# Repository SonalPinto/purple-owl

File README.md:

# Purple Owl

The Purple Owl is a uniform row staggered 60% keyboard designed around ortholinear 1u keycaps and hotswap sockets.

## News
- The prototype appeared on KBD.news! [Link](https://kbd.news/Purple-Owl-1581.html)
- 🎉 PurpleOwl wins 2nd place 🥈 in the [XIAO Mechanical Keyboard Contest](https://www.seeedstudio.com/seeed-fusion-diy-xiao-mechanical-keyboard-contest.html) 🎉

## Layout
The Purple Owl was inspired off the works of Ziptyze with their Zlant (4x12) and ZlantXL (5x12). It is almost like a staggered 5-row Preonic but with more columns a narrow bottom row to offer the visual aesthetic of four dominant rows like a Plank. Each row has a 0.25u stagger unlike a traditional row-stagger. There are 14 columns to accommodate the outer symbols (`-=[]\`). The right shift can be traded in for an arrow cluster. The ctrl, shift and other mods are designed to be under the thumbs with a symmetric bottom row that has a 2u surrounded by two 1u on each side. The board runs on [KMK](http://kmkfw.io/), so the keys can be freely mapped.

Link to the base layout at [Keyboard Layout Editor](http://www.keyboard-layout-editor.com/#/gists/7c51d0df5eb78da5dd614ee6019f13bc). KLE Raw is also available [here](purple-owl-kle.txt)

## Electronics
Instead of a traditional diode matrix, the Purple Owl implements a **scan chain** to poll the state of its switches using only 3 logic pins. This opens the door to support a wide variety of off-the-shelf microcontrollers including the Pro Micro layout variants popular in the mechanical keyboard community. KMK supports a scan chain scanner by default. So, any CircuitPython compatible board with the pinouts shown below should snap into Purple Owl. There is a solder jumper to select between two popular layouts - the Pro Micro variant and the Seeed XIAO variant. The Purple Owl design needs two power pins (3V3 and GND) and three logic pins (CLK, DATA, LATCH).

> While, I currently have a bunch of RP2040 boards in various layouts, I eventually might test out KMK BLE wireless with some CircuitPython compatible nrf52840 board like the nice!nano, [Seeed nrf52840](https://www.seeedstudio.com/Seeed-XIAO-BLE-Sense-nRF52840-p-5253.html) or Adafruit QTPy Bluefruit (doesn't exist yet?). Anything with a JST connector for the battery.

## Seeed XIAO Mechanical Keyboard Contest
I came across an article for this [contest](https://www.seeedstudio.com/seeed-fusion-diy-xiao-mechanical-keyboard-contest.html) on [KBD.news](https://kbd.news/). The Purple Owl was designed to be powered by a [Seeed XIAO RP2040](https://www.seeedstudio.com/XIAO-RP2040-v1-0-p-5026.html) (or any CircuitPython compatible Seeed XIAO for that matter) and will be my entry in the contest! Seeed is sponsoring two fully [assembled PCBs](https://www.seeedstudio.com/pcb-assembly.html) - and that is an opportunity I simply couldn't pass on.

The tiny size of the Seeed XIAO RP2040 will be perfect to highlight the GPIO-efficient scan-chain design. Aside from the 61 switches, the Seeed XIAO RP2040 will drive 16 underglow LEDs which will look stunning in a laser cut case.

## Gallery

## PCB

### Externals
- Acheron MX footprints ([link](https://github.com/AcheronProject/acheron_MXH.pretty.git)) for Kailh hotswap sockets.
- Geometric animals art for the silkscreen ([link](https://www.etsy.com/listing/873524342/geometric-animals-bundle-svg-linear]))
- JLCPCB Tools for Kicad ([link](https://github.com/Bouni/kicad-jlcpcb-tools)) to generate the gerbers and assembly files for JLCPCB.

### Prototype v0.1
To get a feel for the layout I prototyped a board that runs off a RP2040 microcontroller, the Waveshare RP2040 Zero. When I started the prototype, I intended for the the final Purple Owl PCB to have all electronics integrated on the board, including the RP2040. The prototype PCB is simply a diode matrix of hotswap sockets and diodes hooked up to the Zero. No LEDs or anything fancy yet.

I referred to the "recommended minimums" on [Acheron Setup](http://acheronproject.com/acheron_setup/acheron_setup/) for board rules which are more constrained for some fields that the default JLCPCB setup. Laying out the switches is a cakewalk once you set the grid to 19.05mm (1u or 0.75in). For the stagger, set the grid to 4.7625mm (0.25u or 19.05/4mm). The controller is tilted by 26' which is along the ~~z~~slant of the columns.

I checked for clearance pretty early on as soon as I had the swtiches and controller laid out to make sure the slightly tilted controller and USB cable seemed ok on the right side. I printed half(~ish) the layout flipped on paper to scale.

For assembly, I wanted to trial JLCPCB's assembly service - especially for hotswap sockets. While, I could simply solder the sockets myself, I was curious about JLCPCB's work. And, if it did work, then building the proper Purple Owl would be fairly turnkey.

The footprint for the JLCPCB [part](https://jlcpcb.com/partdetail/Kailh-CPG151101S11/C2803348) for the Kailh hotswap socket is centered around the socket itself. But, the switch footprint on the PCB is centered around the stem hole. So, I wrote a [small python snippet](pcb/tools/fix_pos.py) to fix the socket position and rotation in the POS assembly file. Below, you can see how it looks before (right) and after (left) the fix on the JLCPCB assembly preview.

The cost for the PCB fabrication and assembly came up to $85 for 5 boards assembled. The 305 hotswap sockets (61 per board) going at 78 cents a piece for a total of about $24. In hindsight, I should have just assembled 2 boards considering this was a prototype, but my excitement got the better of me.

> Firmware Note: The Zero supports CircuitPython and thus, KMK. So, not much work to be done aside from the KMK config for the matrix. I'd need to add CircuitPython support for the RP2040 layout integrated on the proper Purple Owl (if I went that route), but that seems easy looking at [how it was ported](https://sourcegraph.com/github.com/adafruit/circuitpython/-/tree/ports/raspberrypi/boards/waveshare_rp2040_zero) for the Zero.

### Revelation: The Scan Chain

A while back, I had considered shift registers for scanning the switch matrix in passing when I had read this [Hackaday article](https://hackaday.com/2018/09/30/whats-the-cheapest-way-to-scan-lots-of-buttons/). Along the lines of using 2 shift registers for an 8x8 matrix - one serial-to-parallel to drive the columns and a parallel-to-serial to poll the rows. While this would use only two 8-bit shift registers, I'd still need diodes per switch for NKRO. However, I'd need no more than 5-6 pins to interface with the switch matrix over the two shift registers. At first glance, the approach didn't really seem any better than using a traditional diode matrix and routing the columns and rows to the IOs of the microcontroller (especially since I was considering integrating the RP2040 on the board).

Then, I stumbled upon an article for the [Hello World Smart Keyboard](https://kbd.news/Hello-Word-Smart-Keyboard-1569.html) project when Dovenyi posted their [#89 issue of the KBD News Digest](https://www.reddit.com/r/MechanicalKeyboards/comments/wdgbuy/keyboard_builders_digest_issue_89/) on r/mk. It was a curiously interesting design with 74HC165 shift registers polling _all_ switches latched in parallel along a 1xN matrix. Surely, this would need a lot of shift registers (one IC per 8 keys) and pull up resistors per switch. So, in terms of parts, the design used relatively more parts (and proper active components). Nonetheless, the most attractive part of the design was that it needed merely 3 pins to interface with the matrix.

While I was running a embarrassingly one-sided rubber ducking session with Dovenyi on that reddit thread, I realized something. Using fewer fins suddenly opens up a design where I can attach off-the-shelf (OTS) microcontroller boards right in between the switches (alongside the hotswap sockets) - underneath the switches and not on the side. Because, I'd only need to solder enough headers for functional and mechanical purpose. I could use something tiny like a [Adafruit QTPy RP2040](https://www.adafruit.com/product/4900) or [Pimoroni Tiny RP2040](https://shop.pimoroni.com/products/tiny-2040?variant=39560012234835) and merely use just one side of the pins between the sockets, and some on the other side for mechanical stability.

These uC (microcontroller) boards are typically 700mil wide with their columns of pins 600mil apart. They don't fit around hotswap sockets if you are using all the pins. It does work for soldered switch footprints like in the case of ErgoDash or ErgoTravel, but not for hotswap sockets because of the wider footprint. Hence, in the prototype I had the uC on the side. Secondly, the uC boards that have enough pins for a diode matrix are typically longer than 1U and won't fit across the rows of a row-staggered layout (while they do work for ortho or column staggered layouts). Now, these problems are washed out when you realize that you don't need to drill and solder headers for _all_ the pins. Just enough to get the job done. And, you don't really need to use a small board like the QTPy. Even a KB2040 would work - since you don't have to drill holes across the rows to access all the pins.

I had almost gone down the path of designing an integrated RP2040 board. Researched a bunch of popular designs and minimal RP2040 circuits, and printed all their schematics. I had even picked out the parts on LCSC and had calculated the trace widths and separation required for the differential pair routing for the USB Full Speed mode (90ohm Z_diff). Because I didn't think there was a _good_ design I where I could have the uC board underneath and not on the side...

And now, there was a way.

> Firmware Note: Looks like KMK has a scanner for shift registers ([see](https://github.com/KMKfw/kmk_firmware/blob/master/kmk/scanners/keypad.py)) that wraps CircuitPython's `keypad.ShiftRegisterKeys()`. Great!

### Production v1.0
The design uses 8 74HC165 (TSSOP-16 package) to form the scan chain. 7 of these poll the top 4 rows across 14 columns and the last one polls the bottom row. I've also added 16 underglow LEDs (WS2812B-V5). The scan chain for the first 6 columns is shown below.

Compared to the prototype, the design now has a clean board edge tightly fitting the switches, since the uC now goes underneath. The uC is socketed to the board with through-hole headers. Out of the 14 pins of the Seeed XIAO RP2040, 11 are connected.

There are jumpers to select the 3V3 source depending on the attached uC. And jumpers to select the power source (3.3V or 5V) for the LEDs. Though off-spec, The LEDs work fine on 3.3V, albeit slightly less bright than if powered by 5V. There wasn't enough space (while staying close to the board edge) to allow a through hole header for the 5V, so the design offers a jumper/through-hole that needs to be wired between the board and the jumper site if 5V is desired.

- JP1: Join `1-2` or `2-3` depending on where the 3V3 pin on the uC is. For the Seeed XIAO RP2040 variants short the `1-2`. And, for Pro Micro variants, short `2-3`.
- JP2: Join `1-2` to select the 3.3V source selected by JP1, or connect the 5V to `3` from the uC over a wire and join `2-3`.

For assembly, Seeed is sponsoring two fully assembled boards 🎉

## Firmware

This project was my first experience with CircuitPython, let alone KMK. I am stunned how wasy it was to work with. Never did I think it would take just few lines of python to establish a fully functional keyboard with layers and underglow LEDs.

There are bringup scripts for the both PCB variants which test the PCB and demonstrate interfacing with the keyboard switches using native CircuitPython.
- [v0.1 bringup](firmware/v0.1/bringup.py) - diode matrix.
- [v1.0 bringup](firmware/v1.0/bringup.py) - scan chain. Using digitalio, it took about 1ms to scan 61 switches. 

The [setup](firmware/v0.1/main.py) for the prototype v0.1 diode matrix was fairly straightforward with KMK. I included three basic layers to start with (I really need the tilde/grave in my line of work). The physical layout of the switches were mapped to the layout with the `coord_mapping` setup.

The [build](firmware/v1.0/main.py) for the v1.0 PCB inherited the same layers. The firmware switched the `scanner` to the `ShiftRegisterKeys()` and updated the `coord_mapping` to the physical layout of the scan chain. KMK offeres a neat `RGB` extension to support the underglow LEDs. The underglow RGB controls are added on a layer. Looking at the sheer simplicity of the [RGB extension](https://github.com/KMKfw/kmk_firmware/blob/master/kmk/extensions/rgb.py) I might consider writing a fancy underglow mode or two. Since, this was a *proper* build, the [`boot.py`](firmware/v1.0/boot.py) was updated with a "dev mode" which hides CircuitPython enumerations (serial, midi and storage) except for the USB HID keyboard.

## Laser cut case

For the case, I had envisioned a laser cut case with 1/8" acrylic layers. With the top layers as dark and the bottom layer as translucent to diffuse the underglow. This was the first time I used Fusion360 as well. Lots of firsts for me in this project. Thankfully, there are a ton of YouTube videos to learn from, and I only need the basics of sketching in 2D to set up the layers for the laser cut case.

Using [plate.keeb.io](https://plate.keeb.io/) I obtained the cut outs for the switches and stabilizer to form the top switch plate. Then, I designed the middle layers to be spaced around the PCB by importing the PCB edge-cuts layer into the design and offset it. All the layers except for the top switch plate have cut outs for the Seeed XIAO RP2040 that is on the underside of the PCB. All the holes are cut out for M2 hardware. I also added holes for some feet that I found on [FlashQuark](https://flashquark.com/product/aluminum-keyboard-feet-set-of-2/). The links to the files for the laser cut case are below.

- [top](case/top.dxf)
- [middle](case/middle.dxf)
- [bottom](case/bottom.dxf)

I used p95 matte black acrylic sourced from a local [TAP plastics](https://www.tapplastics.com/plastics/custom-cut-to-size-plastic-sheets/acrylic-plexiglass-sheets) for the top three layers (1xtop, 2xmiddle), and a satinice acrylic for the bottom layer.

## Credits
- Layout inspired by Ziptyze's [Zlant](https://1upkeyboards.com/shop/keyboard-kits/diy-40-kits/zlant-40-acrylic-keyboard-kit/) and [ZlantXL](https://1upkeyboards.com/shop/keyboard-kits/diy-40-kits/zlantxl-50-mechanical-keyboard-kit/).
- Electronics inspired by Zhihui's [HanWen](https://github.com/peng-zhihui/HelloWord-Keyboard) and Tzarc's [Ghoul](https://github.com/tzarc/ghoul) which use shift registers to scan the matrix.
- Dovenyi and [Keyboard Builder's Digest](https://kbd.news/).
- Seeed DIY XIAO Mechanical Keyboard Contest, [Link](https://www.seeedstudio.com/seeed-fusion-diy-xiao-mechanical-keyboard-contest.html).
- Photography by Wife 😘.

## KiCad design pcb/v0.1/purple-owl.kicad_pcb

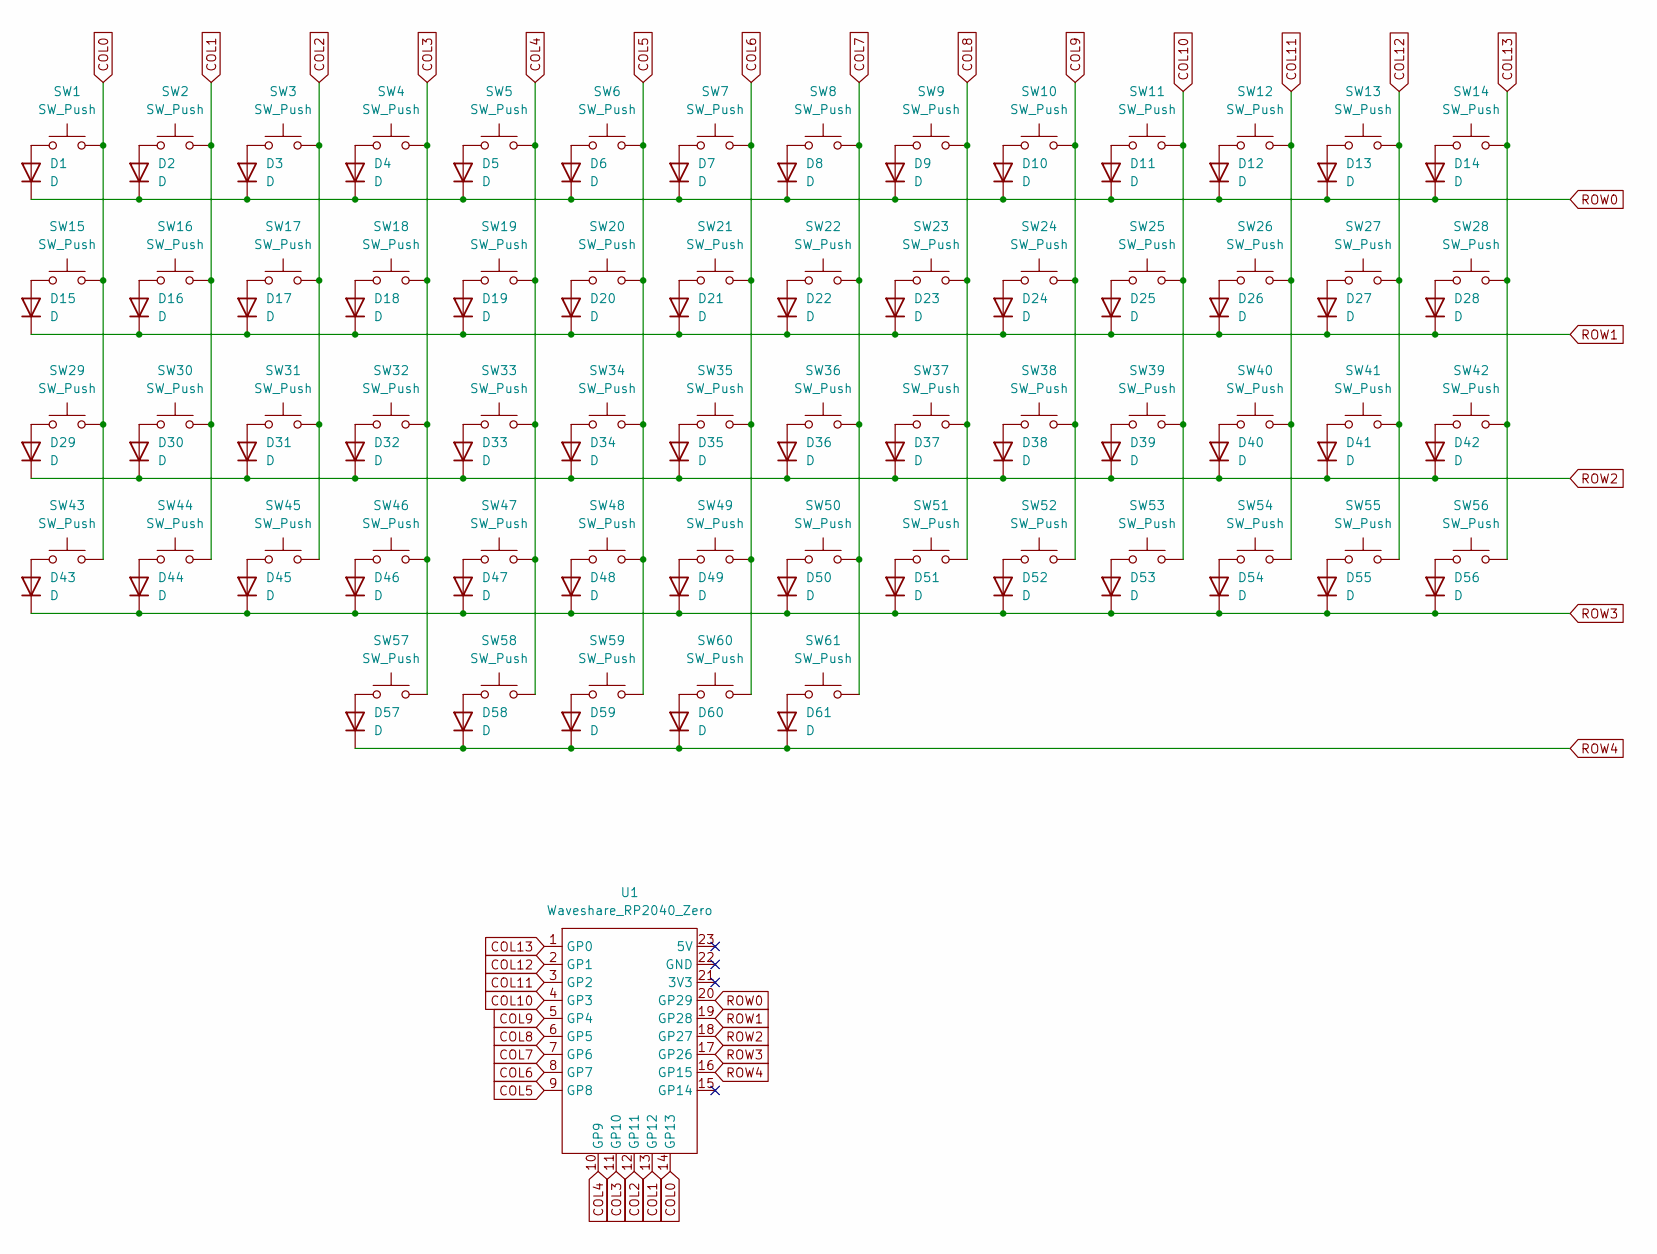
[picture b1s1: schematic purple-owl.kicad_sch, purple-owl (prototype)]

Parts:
D1, D2, D3, D4, D5, D6, D7, D8, D9, D10, D11, D12, D13, D14, D15, D16, D17, D18, D19, D20, D21, D22, D23, D24, D25, D26, D27, D28, D29, D30, D31, D32, D33, D34, D35, D36, D37, D38, D39, D40, D41, D42, D43, D44, D45, D46, D47, D48, D49, D50, D51, D52, D53, D54, D55, D56, D57, D58, D59, D60, D61: D; D_SOD-123
SW1, SW2, SW3, SW4, SW5, SW6, SW7, SW8, SW9, SW10, SW11, SW12, SW13, SW14, SW15, SW16, SW17, SW18, SW19, SW20, SW21, SW22, SW23, SW24, SW25, SW26, SW27, SW28, SW29, SW30, SW31, SW32, SW33, SW34, SW35, SW36, SW37, SW38, SW39, SW40, SW41, SW42, SW43, SW44, SW45, SW46, SW47, SW48, SW49, SW50, SW51, SW52, SW53, SW54, SW55, SW56, SW57, SW58, SW60, SW61: SW_Push; MX100H
SW59: SW_Push; MX200HR
U1: Waveshare_RP2040_Zero

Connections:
COL0: SW1.2, SW15.2, SW29.2, SW43.2, U1.14 (GP13)
COL1: SW2.2, SW16.2, SW30.2, SW44.2, U1.13 (GP12)
COL2: SW3.2, SW17.2, SW31.2, SW45.2, U1.12 (GP11)
COL3: SW4.2, SW18.2, SW32.2, SW46.2, SW57.2, U1.11 (GP10)
COL4: SW5.2, SW19.2, SW33.2, SW47.2, SW58.2, U1.10 (GP9)
COL5: SW6.2, SW20.2, SW34.2, SW48.2, SW59.2, U1.9 (GP8)
COL6: SW7.2, SW21.2, SW35.2, SW49.2, SW60.2, U1.8 (GP7)
COL7: SW8.2, SW22.2, SW36.2, SW50.2, SW61.2, U1.7 (GP6)
COL8: SW9.2, SW23.2, SW37.2, SW51.2, U1.6 (GP5)
COL9: SW10.2, SW24.2, SW38.2, SW52.2, U1.5 (GP4)
COL10: SW11.2, SW25.2, SW39.2, SW53.2, U1.4 (GP3)
COL11: SW12.2, SW26.2, SW40.2, SW54.2, U1.3 (GP2)
COL12: SW13.2, SW27.2, SW41.2, SW55.2, U1.2 (GP1)
COL13: SW14.2, SW28.2, SW42.2, SW56.2, U1.1 (GP0)
unnamed: D1.2 (A), SW1.1
unnamed: D2.2 (A), SW2.1
unnamed: D3.2 (A), SW3.1
unnamed: D4.2 (A), SW4.1
unnamed: D5.2 (A), SW5.1
unnamed: D6.2 (A), SW6.1
unnamed: D7.2 (A), SW7.1
unnamed: D8.2 (A), SW8.1
unnamed: D9.2 (A), SW9.1
unnamed: D10.2 (A), SW10.1
unnamed: D11.2 (A), SW11.1
unnamed: D12.2 (A), SW12.1
unnamed: D13.2 (A), SW13.1
unnamed: D14.2 (A), SW14.1
unnamed: D15.2 (A), SW15.1
unnamed: D16.2 (A), SW16.1
unnamed: D17.2 (A), SW17.1
unnamed: D18.2 (A), SW18.1
unnamed: D19.2 (A), SW19.1
unnamed: D20.2 (A), SW20.1
unnamed: D21.2 (A), SW21.1
unnamed: D22.2 (A), SW22.1
unnamed: D23.2 (A), SW23.1
unnamed: D24.2 (A), SW24.1
unnamed: D25.2 (A), SW25.1
unnamed: D26.2 (A), SW26.1
unnamed: D27.2 (A), SW27.1
unnamed: D28.2 (A), SW28.1
unnamed: D29.2 (A), SW29.1
unnamed: D30.2 (A), SW30.1
unnamed: D31.2 (A), SW31.1
unnamed: D32.2 (A), SW32.1
unnamed: D33.2 (A), SW33.1
unnamed: D34.2 (A), SW34.1
unnamed: D35.2 (A), SW35.1
unnamed: D36.2 (A), SW36.1
unnamed: D37.2 (A), SW37.1
unnamed: D38.2 (A), SW38.1
unnamed: D39.2 (A), SW39.1
unnamed: D40.2 (A), SW40.1
unnamed: D41.2 (A), SW41.1
unnamed: D42.2 (A), SW42.1
unnamed: D43.2 (A), SW43.1
unnamed: D44.2 (A), SW44.1
unnamed: D45.2 (A), SW45.1
unnamed: D46.2 (A), SW46.1
unnamed: D47.2 (A), SW47.1
unnamed: D48.2 (A), SW48.1
unnamed: D49.2 (A), SW49.1
unnamed: D50.2 (A), SW50.1
unnamed: D51.2 (A), SW51.1
unnamed: D52.2 (A), SW52.1
unnamed: D53.2 (A), SW53.1
unnamed: D54.2 (A), SW54.1
unnamed: D55.2 (A), SW55.1
unnamed: D56.2 (A), SW56.1
unnamed: D57.2 (A), SW57.1
unnamed: D58.2 (A), SW58.1
unnamed: D59.2 (A), SW59.1
unnamed: D60.2 (A), SW60.1
unnamed: D61.2 (A), SW61.1
ROW0: D1.1 (K), D2.1 (K), D3.1 (K), D4.1 (K), D5.1 (K), D6.1 (K), D7.1 (K), D8.1 (K), D9.1 (K), D10.1 (K), D11.1 (K), D12.1 (K), D13.1 (K), D14.1 (K), U1.20 (GP29)
ROW1: D15.1 (K), D16.1 (K), D17.1 (K), D18.1 (K), D19.1 (K), D20.1 (K), D21.1 (K), D22.1 (K), D23.1 (K), D24.1 (K), D25.1 (K), D26.1 (K), D27.1 (K), D28.1 (K), U1.19 (GP28)
ROW2: D29.1 (K), D30.1 (K), D31.1 (K), D32.1 (K), D33.1 (K), D34.1 (K), D35.1 (K), D36.1 (K), D37.1 (K), D38.1 (K), D39.1 (K), D40.1 (K), D41.1 (K), D42.1 (K), U1.18 (GP27)
ROW3: D43.1 (K), D44.1 (K), D45.1 (K), D46.1 (K), D47.1 (K), D48.1 (K), D49.1 (K), D50.1 (K), D51.1 (K), D52.1 (K), D53.1 (K), D54.1 (K), D55.1 (K), D56.1 (K), U1.17 (GP26)
ROW4: D57.1 (K), D58.1 (K), D59.1 (K), D60.1 (K), D61.1 (K), U1.16 (GP15)

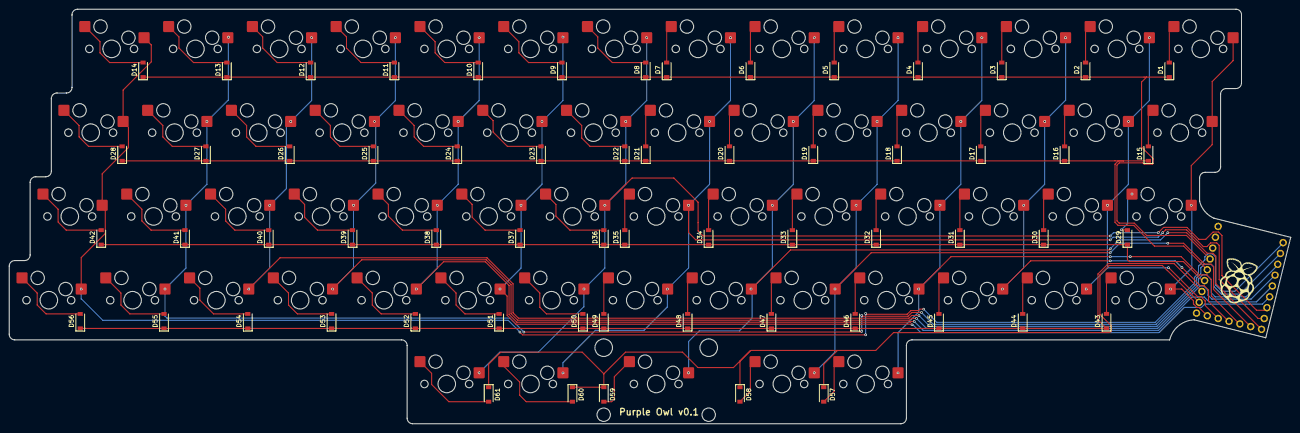
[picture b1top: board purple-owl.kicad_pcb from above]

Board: 2 copper layers, 291.4 x 94.3 mm, 123 parts (1 on the bottom side), 80 nets.

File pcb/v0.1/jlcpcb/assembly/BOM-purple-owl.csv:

Comment,Designator,Footprint,LCSC
SW_Push,"SW1,SW10,SW11,SW12,SW13,SW14,SW15,SW16,SW17,SW18,SW19,SW2,SW20,SW21,SW22,SW23,SW24,SW25,SW26,SW27,SW28,SW29,SW3,SW30,SW31,SW32,SW33,SW34,SW35,SW36,SW37,SW38,SW39,SW4,SW40,SW41,SW42,SW43,SW44,SW45,SW46,SW47,SW48,SW49,SW5,SW50,SW51,SW52,SW53,SW54,SW55,SW56,SW57,SW58,SW59,SW6,SW60,SW61,SW7,SW8,SW9",MX100H,C2803348
D,"D1,D10,D11,D12,D13,D14,D15,D16,D17,D18,D19,D2,D20,D21,D22,D23,D24,D25,D26,D27,D28,D29,D3,D30,D31,D32,D33,D34,D35,D36,D37,D38,D39,D4,D40,D41,D42,D43,D44,D45,D46,D47,D48,D49,D5,D50,D51,D52,D53,D54,D55,D56,D57,D58,D59,D6,D60,D61,D7,D8,D9",D_SOD-123,C81598

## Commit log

2022-07-31 First Commit
    - Add Purple Owl prototype PCB
    - Purple Owl kicad symbols and footprints
    - README
2022-08-02 Add QTPy RP2040 symbol and footprint
    - Add Adafruit QTPy RP2040 symbol and footprint
    - Update story on README
2022-08-03 Update README with WIP badge
2022-08-04 Open pcb design for v1.0
    - Schematic for v1.0 with 74HC165 shift registers for the 61 keys
    - Matrix is polled using 5 pins - 3V3, GND, Latch, Data and Clock
    - Solder jumper for 3V3 compatibility between KB2040 (ProMicro variant)
    and QTPy layout (Waveshare RP2040 Zero, Pimoroni Tiny RP2040, Seeed Xiao
    RP2040)
    - Alternate few-pin footprints for Adafruit QTPy RP2040 and KB2040
2022-08-05 Add pinout gist to README
2022-08-05 Update assets and center images in README
2022-08-12 Update 1.0 Schematic
    - Add 16 underglow LEDs (ws2812b-v5)
    - Jumper for LED power source (3.3V or 5V)
    - Add footprints for jumpers
    - ComboJumper: through-hole/solder combo jumper
    - SolderJumper: regular solder jumper with mask between pads
    - Update README
2022-08-16 Push towards v1.0
    - Layout for v1.0
    - Fab files for Seeed and JLCPCB
    - Updated footprints
    - Updated README
    - Update JLCPCB position fix script
2022-08-16 Update pinout in README
    - Add graphic for Seeed XIAO RP2040
2022-08-16 Crop image for README
2022-08-24 KMK Firmware for v0.1
    - bringup (basic keytester) and production firmware for v0.1 (diode matrix keyboard)
    - basic boot.py
2022-09-04 Firmware for v1.0
    - Scan chain PCB tester/bringup util
    - KMK keyboard build for v1.0 - with RGB extension for underglow
    - boot.py with "dev mode" (press ESC when plugging in) to enable CircuitPython Dev mode. Else the CircuitPython drive enumeration is disabled. Also disables serial, midi, etc.
2022-09-04 Cleanup prototype v0.1 boot.py
2022-09-04 Update README with details about Firmware
2022-09-04 Fix line-endings in fix_pos.py
2022-09-15 photos
2022-09-15 edited photos
2022-09-15 Update README, add dark3
2022-09-15 rename asset
2022-09-15 More photos
2022-09-16 daylight photos
2022-09-16 remove unlit board photos
2022-09-16 update photos
2022-09-17 resize photo
2022-09-17 Add files for the case
2022-09-17 remove stray file
2023-01-30 Add the good news
2023-01-30 Consolidate news in README

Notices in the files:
pcb/v0.1/purple-owl.kicad_pcb:
License: MIT
